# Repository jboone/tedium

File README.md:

# tedium

TDM telephony experimentation

## Dependencies

* `oss-cad-suite`: open-source digital design and verification tools, with [nightly binary builds](https://github.com/YosysHQ/oss-cad-suite-build).
* [`poetry`](https://python-poetry.org/): Python dependencies and packaging management tool.
* `g++-riscv64-linux-gnu`
* `rustup toolchain install stable -t riscv32i-unknown-none-elf`

## Installation

Clone this repository, and generally follow these steps:

```bash
$ cd tedium
# Grant access through `udev` to the FTDI JTAG interface on the Tedium board.
$ sudo ln -sf ./99-tedium.rules /etc/udev/rules.d/
$ sudo udevadm control --reload-rules && sudo udevadm trigger
#
$ pip3 install poetry --user
# Might need to log out and in to get ~/.local/bin in PATH.
# Or, `source ~/.profile`.
# Set up virtual environment, download and install dependencies
$ poetry install
# Enter poetry shell
$ poetry shell
# Include OSS CAD Suite tools in PATH
$ export PATH="/home/jboone/src/fpga/oss-cad-suite/bin:$PATH"
# Build and download FPGA bitstream
# LUNA_AVOID_BLOCKRAM required for reliable USB enumeration as of 2022/May/02.
$ LUNA_AVOID_BLOCKRAM=1 applets/tedium-fpga
# After the bitstream is generated, you can inspect the results in the `build` directory.
# Initialize the framer/LIU
$ cargo run --release --bin tedium-tool -- init
# Run the host-side audio and event engine
$ cargo run --release --bin tedium-tool -- monitor
```

NOTE: My Tedium .venv got weird when I had the "OSS CAD Suite" environment already enabled.
Poetry would download dependencies on `poetry install` or `poetry update`, but would then
delete them when running `poetry run` or `poetry shell`.

## Testing

Unit tests may be run like this:

```bash
$ python3 -m unittest tests.hdl.tx_usb_to_fifo
# Or the name of any other HDL test module you want to run/simulate.
```

## USB Debugging

```bash
$ sudo cat /sys/kernel/debug/usb/devices
$ sudo cat /sys/kernel/debug/dynamic_debug/control | grep "snd_usb_audio"
$ sudo echo 'file sound/usb/* +p' >/sys/kernel/debug/dynamic_debug/control
$ sudo sysctl -w kernel.printk=7 # debug-level messages
$ sudo sysctl kernel.printk
```

### Using Wireshark

```bash
$ sudo modprobe usbmon
$ sudo wireshark
# Capture stuff
```

Wireshark filters that might be of use:

```
# Find USB IN on endpoint 1, where the frame of completed inbound URBs is not the typical length.
# This helps find where the async audio input FIFO level is wrapping around.
usb.endpoint_address.number==1 && usb.endpoint_address.direction==IN && usb.urb_type=='C' && frame.len != 1728
# Set the time reference at an interesting record in Wireshark, disable view filtering, and work from there.
# Note that "marked" records appear regardless of whether they match the view filter, which is very handy.
# Now match on USB OUT records that have been submitted (pending transmission)
usb.endpoint_address.number==1 && usb.endpoint_address.direction==OUT && usb.urb_type=='S'
```

However, it seems like Wireshark isn't showing complete URB buffer contents?

## Trouble With Real-Time Kit

```bash
# Is there an `rtkit` user?
$ getent passwd rtkit
# Is there an `rtkit*` user?
$ ps ax | grep -i rtkit
# Check that RTKit is actually changing our process/thread priority:
$ journalctl -e -t rtkit-daemon
# `ulimit` values:
$ ulimit -a
```

## Use

See [the software README](tedium/README.md) for information on how to use `tedium-tool` to interact with the hardware over USB.

## License

This software and gateware in this project is licensed under the [BSD 3-Clause License](LICENSE-BSD-3-Clause).

The hardware is licensed under the [CERN Open Hardware Licence Version 2 - Permissive](LICENSE-CERN-OHL-P-v2).

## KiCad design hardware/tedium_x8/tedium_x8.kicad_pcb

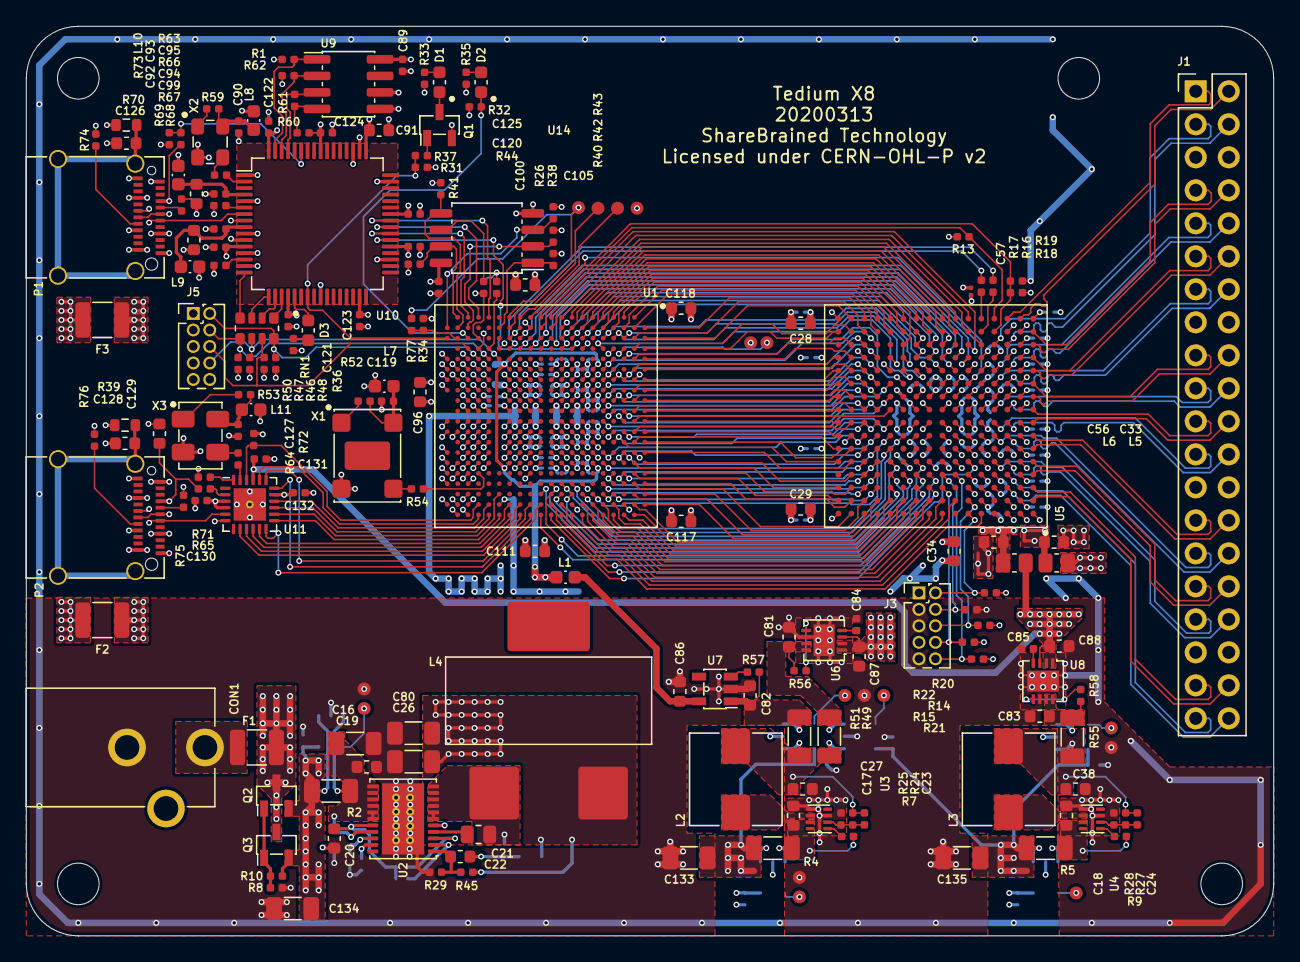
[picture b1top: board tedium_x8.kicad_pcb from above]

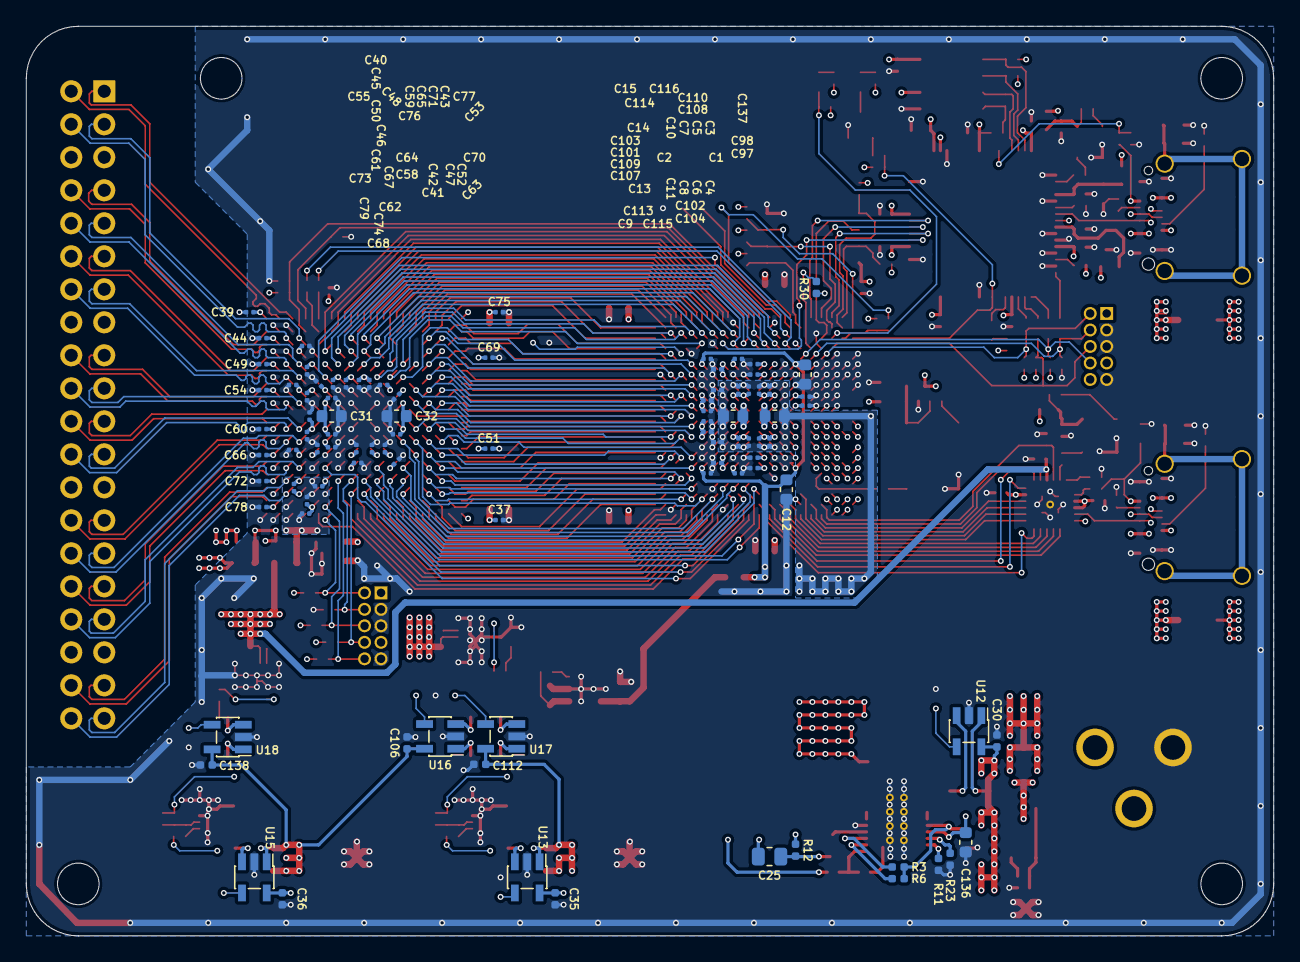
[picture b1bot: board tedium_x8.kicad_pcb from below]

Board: 4 copper layers, 96.0 x 70.0 mm, 283 parts (92 on the bottom side), 290 nets.

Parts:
C1, C2, C28, C29, C31, C32, C33, C34, C56, C91, C92, C93, C96, C105, C111, C117, C118: 10U; IPC_CAPC160X80X90L35N
C3, C4, C5, C6, C7, C8, C9, C10, C11, C13, C14, C15, C37, C39, C40, C41, C42, C43, C44, C45, C46, C47, C48, C49, C50, C51, C52, C53, C54, C55, C57, C58, C59, C60, C61, C62, C63, C64, C65, C66, C67, C68, C69, C70, C71, C72, C73, C74, C75, C76, C77, C78, C79, C97, C98, C101, C102, C103, C104, C107, C108, C109, C110, C113, C114, C115, C116: 100N; IPC_CAPC60X30X33L15N
C12, C20, C129, C137: 1U; IPC_CAPC160X80X90L35N
C16: 47U; IPC_CAPC320X160X180L55N
C17, C18, C19, C81, C82, C83, C86, C87, C88, C136: 4U7; IPC_CAPC160X80X90L35N
C21, C25: 100N; IPC_CAPC200X125X135L45N
C22: 1N2; IPC_CAPC160X80X90L35N
C23, C24: 120P; IPC_CAPC100X50X55L25N
C26, C80: 100U; IPC_CAPC320X160X180L55N
C27, C38: 22U; IPC_CAPC160X80X90L35N
C30, C35, C36, C89, C94, C95, C99, C100, C106, C112, C120, C121, C122, C123, C124, C125, C130, C131, C132, C138: 100N; IPC_CAPC100X50X55L25N
C84, C85: ?; IPC_CAPC100X50X55L25N
C90, C119, C127: 10N; IPC_CAPC100X50X55L25N
C126, C128: 100N; IPC_CAPC160X80X90L35N
C133, C134, C135: 22U; IPC_CAPC320X160X180L55N
CON1: BARREL_JACK; PJ-102AH
D1, D2, D3: LED; IPC_LEDC1608X90L40N
F1, F2, F3: Polyfuse_Small; IPC_FUSSC257X321X120L50N
H1, H2, H3, H4: MountingHole; MountingHole_3.2mm_M3
J1: Conn_02x20_Odd_Even; PinHeader_2x20_P2.54mm_Vertical
J3: DNP; PinHeader_2x05_P1.27mm_Vertical
J5: Conn_ARM_JTAG_SWD_10; PinHeader_2x05_P1.27mm_Vertical
L1, L7, L8, L9, L10, L11: L_Small; IPC_BEADC160X80X95L40N
L2, L3: 470N; WE-HCI_7050
L4: 1U; SER1590
L5, L6: L_Small; IPC_BEADC200X125X105L50N
P1, P2: USB_C; 12401610E4#2A
Q1: BC817; IPC_SOT23-3P95_237X112L50X42N
Q2, Q3: Q_PMOS_GSD; IPC_SOT23-3P95_237X112L50X42N
R1, R29, R31, R37, R41, R42, R43, R44, R52, R53, R59, R60, R62, R65, R69: 10K; IPC_RESC100X50X40L25N
R2: 0R01; IPC_RESC320X160X89L51N
R3, R6, R7, R9, R23, R25, R28, R56, R57, R58: 100K; IPC_RESC100X50X40L25N
R4, R5, R49, R51, R55: 0R1; IPC_RESC320X160X89L51N
R8, R10: 30K; IPC_RESC100X50X40L25N
R11: 68K1; IPC_RESC100X50X40L25N
R12: 432R; IPC_RESC100X50X40L25N
R13, R19, R30: 1K; IPC_RESC100X50X40L25N
R14, R15, R18, R20, R22: DNP; IPC_RESC100X50X40L25N
R16, R17, R54, R63, R64: 10R; IPC_RESC100X50X40L25N
R21, R32, R34, R38, R40, R46, R47, R48, R50, R68, R72: 4K7; IPC_RESC100X50X40L25N
R24: 536K; IPC_RESC100X50X40L25N
R26: 50R; IPC_RESC100X50X40L25N
R27: 280K; IPC_RESC100X50X40L25N
R33, R35, R36, R61, R67: 2K2; IPC_RESC100X50X40L25N
R39, R70: 330R; IPC_RESC160X80X55L25N
R45: 7K68; IPC_RESC100X50X40L25N
R66: 12K; IPC_RESC100X50X40L25N
R71: 8K06; IPC_RESC100X50X40L25N
R73, R74, R75, R76: 5K1; IPC_RESC100X50X40L25N
R77: 100R; IPC_RESC100X50X40L25N
RN1: 100R; IPC_RESCAXS8P80_320X160X60L30X45N
TP1: V1P1_I; TP_1MM
TP2: V3P8_I; TP_1MM
TP3: V2P3_I; TP_1MM
TP4: V3P3_I; TP_1MM
TP5: V2P5_I; TP_1MM
TP6: V1P8_I; TP_1MM
TP7, TP8, TP9, TP10: TestPoint; TP_1MM
TP11, TP12, TP13, TP14, TP15, TP16: GND; TP_1MM
U1: LFE5U-85F-8BG381; LATTICE_BGA_CABGA381
U2: TPS53318; IPC_SON23P50_600X500X150L50X27T547X324N
U3, U4: TPS62823; IPC_SON8P50_200X150X100L35X25N
U5: XRT86VX38; IPC_BGA256CP100_16X16_1700X1700X178B55N
U6: ADM7171ACPZ-3.3-R7; IPC_SON9P50_300X300X80L40X25T244X160N
U7: ADP150AUJZ-2.5-R7; IPC_SOT23-5P95_280X100L45X40N
U8: ADM7171ACPZ-1.8-R7; IPC_SON9P50_300X300X80L40X25T244X160N
U9: 93LC46C; IPC_SOIC8P127_490X600X175L83X41N
U10: FT2232H; IPC_QFP64P50_1200X1200X160L60X22N
U11: USB3317C-CP; IPC_QFN25P50_400X400X100L40X24T250N
U12, U17: INA180B3; TI_DBV_SOT-23-5
U13, U15, U16, U18: INA180B2; TI_DBV_SOT-23-5
U14: QSPI8; IPC_SOIC8P127_528X790X216L65X41N
X1: 16M384; ASVMB
X2: 12M; IPC_OSCCC320X250X120L75X100N
X3: 26M; IPC_OSCSC4P254_500X320X140L100X120N

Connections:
+5V: C30.1, C35.1, C36.1, C106.1, C112.1, C133.1, C134.1, C135.1, C138.1, Q2.2, Q3.2, R2.2, R4.2, R5.2, R10.2, U12.1, U12.5, U13.1, U13.5, U15.1, U15.5, U16.5, U17.5, U18.5
/fpga_bank/8KEXTOSC: U1.M1, U5.L6
/fpga_bank/A0: U1.E9, U5.L13
/fpga_bank/A1: U1.C9, U5.L14
/fpga_bank/A2: U1.B9, U5.K15
/fpga_bank/A3: U1.C5, U5.L11
/fpga_bank/A4: U1.D9, U5.K13
/fpga_bank/A5: U1.A9, U5.K16
/fpga_bank/A6: U1.E10, U5.K14
/fpga_bank/A7: U1.B10, U5.J15
/fpga_bank/A8: U1.C10, U5.J14
/fpga_bank/A9: U1.C11, U5.J13
/fpga_bank/A10: U1.D13, U5.H14
/fpga_bank/A11: U1.A11, U5.H16
/fpga_bank/A12: U1.A12, U5.G16
/fpga_bank/A13: U1.B13, U5.F16
/fpga_bank/A14: U1.H17, U5.G11
/fpga_bank/ACK0#: U1.A5, U5.N15
/fpga_bank/ACK1#: U1.A6, U5.M15
/fpga_bank/ALE: U1.A10, U5.J16
/fpga_bank/CLKREF: R54.2, U1.U16
/fpga_bank/CS#: U1.C14, U5.F14
/fpga_bank/D0: U1.E8, U5.M14
/fpga_bank/D1: U1.D10, U5.L12
/fpga_bank/D2: U1.E11, U5.K12
/fpga_bank/D3: U1.B11, U5.J12
/fpga_bank/D4: U1.C12, U5.H13
/fpga_bank/D5: U1.E14, U5.G14
/fpga_bank/D6: U1.F18, U5.G12
/fpga_bank/D7: U1.C15, U5.G13
/fpga_bank/E1OSCCLK: R16.1, U1.P4
/fpga_bank/FPGA_C4: TP10.1, U1.C4
/fpga_bank/FPGA_N1: TP7.1, U1.N1
/fpga_bank/FPGA_P2: TP9.1, U1.P2
/fpga_bank/FRM_RESET#: R18.1, R19.2, U1.L1, U5.R4
/fpga_bank/FT_SCLK: U1.H4, U10.38
/fpga_bank/INT#: U1.B12, U5.H15
/fpga_bank/MCLKIN: U1.K20, U5.E6
/fpga_bank/PCLK: U1.A7, U5.M16
/fpga_bank/PROGRAMN: R77.1, TP8.1, U1.P1
/fpga_bank/PTYPE0: U1.D7, U5.M13
/fpga_bank/PTYPE2: U1.D12, U5.H12
/fpga_bank/RD#: U1.B8, U5.L15
/fpga_bank/RDY#: U1.A8, U5.L16
/fpga_bank/REQ0#: U1.B6, U5.N16
/fpga_bank/REQ1#: U1.A4, U5.R16
/fpga_bank/RXCASYNC0: U1.F20, U5.A9
/fpga_bank/RXCASYNC1: U1.K17, U5.D11
/fpga_bank/RXCASYNC2: U1.E17, U5.D13
/fpga_bank/RXCASYNC3: U1.C16, U5.E13
/fpga_bank/RXCASYNC4: U1.B3, U5.R14
/fpga_bank/RXCASYNC5: U1.C2, U5.R12
/fpga_bank/RXCASYNC6: U1.J3, U5.N9
/fpga_bank/RXCASYNC7: U1.F3, U5.M8
/fpga_bank/RXCRCSYNC0: U1.G20, U5.A8
/fpga_bank/RXCRCSYNC1: U1.L20, U5.C10
/fpga_bank/RXCRCSYNC2: U1.E18, U5.C14
/fpga_bank/RXCRCSYNC3: U1.J17, U5.E12
/fpga_bank/RXCRCSYNC4: U1.B4, U5.R15
/fpga_bank/RXCRCSYNC5: U1.B2, U5.R13
/fpga_bank/RXCRCSYNC6: U1.F2, U5.R9
/fpga_bank/RXCRCSYNC7: U1.M4, U5.N7
/fpga_bank/RXSCLK0: U1.E19, U5.B10
/fpga_bank/RXSCLK1: U1.J18, U5.D12
/fpga_bank/RXSCLK2: U1.B17, U5.A15
/fpga_bank/RXSCLK3: U1.G18, U5.F12
/fpga_bank/RXSCLK4: U1.A3, U5.T15
/fpga_bank/RXSCLK5: U1.D1, U5.T11
/fpga_bank/RXSCLK6: U1.J4, U5.P9
/fpga_bank/RXSCLK7: U1.K3, U5.M7
/fpga_bank/RXSER0: U1.H20, U5.B7
/fpga_bank/RXSER1: U1.D19, U5.B11
/fpga_bank/RXSER2: U1.A18, U5.B14
/fpga_bank/RXSER3: U1.B16, U5.B16
/fpga_bank/RXSER4: U1.B5, U5.P15
/fpga_bank/RXSER5: U1.E2, U5.P11
/fpga_bank/RXSER6: U1.E1, U5.T10
/fpga_bank/RXSER7: U1.L4, U5.P8
/fpga_bank/RXSERCLK0: U1.G19, U5.B8
/fpga_bank/RXSERCLK1: U1.E20, U5.A10
/fpga_bank/RXSERCLK2: U1.D18, U5.C13
/fpga_bank/RXSERCLK3: U1.A15, U5.D15
/fpga_bank/RXSERCLK4: U1.E7, U5.P14
/fpga_bank/RXSERCLK5: U1.C1, U5.T12
/fpga_bank/RXSERCLK6: U1.C3, U5.M10
/fpga_bank/RXSERCLK7: U1.J1, U5.R6
/fpga_bank/RXSYNC0: U1.F19, U5.B9
/fpga_bank/RXSYNC1: U1.D20, U5.A11
/fpga_bank/RXSYNC2: U1.B19, U5.A13
/fpga_bank/RXSYNC3: U1.B15, U5.C16
/fpga_bank/RXSYNC4: U1.C7, U5.N13
/fpga_bank/RXSYNC5: U1.E3, U5.N11
/fpga_bank/RXSYNC6: U1.F1, U5.T9
/fpga_bank/RXSYNC7: U1.H2, U5.R7
/fpga_bank/RXTSEL: U1.J19, U5.A5
/fpga_bank/T1OSCCLK: R17.1, U1.P3
/fpga_bank/TXMSYNC0: U1.J20, U5.D9
/fpga_bank/TXMSYNC1: U1.C20, U5.A12
/fpga_bank/TXMSYNC2: U1.A16, U5.C15
/fpga_bank/TXMSYNC3: U1.C17, U5.E14
/fpga_bank/TXMSYNC4: U1.E6, U5.P13
/fpga_bank/TXMSYNC5: U1.D2, U5.R11
/fpga_bank/TXMSYNC6: U1.G2, U5.R8
/fpga_bank/TXMSYNC7: U1.N4, U5.N6
/fpga_bank/TXON: R13.2, U1.L2, U5.T4
/fpga_bank/TXSER0: U1.L18, U5.E10
/fpga_bank/TXSER1: U1.H18, U5.C12
/fpga_bank/TXSER2: U1.D16, U5.D14
/fpga_bank/TXSER3: U1.A13, U5.F15
/fpga_bank/TXSER4: U1.D3, U5.N12
/fpga_bank/TXSER5: U1.H3, U5.P10
/fpga_bank/TXSER6: U1.G1, U5.T8
/fpga_bank/TXSER7: U1.K1, U5.P5
/fpga_bank/TXSERCLK0: U1.K18, U5.D10
/fpga_bank/TXSERCLK1: U1.A19, U5.B13
/fpga_bank/TXSERCLK2: U1.A17, U5.B15
/fpga_bank/TXSERCLK3: U1.C13, U5.E16
/fpga_bank/TXSERCLK4: U1.A2, U5.T14
/fpga_bank/TXSERCLK5: U1.G3, U5.N10
/fpga_bank/TXSERCLK6: U1.H1, U5.T7
/fpga_bank/TXSERCLK7: U1.N3, U5.P6
/fpga_bank/TXSYNC0: U1.K19, U5.C9
/fpga_bank/TXSYNC1: U1.B20, U5.B12
/fpga_bank/TXSYNC2: U1.B18, U5.A14
/fpga_bank/TXSYNC3: U1.A14, U5.E15
/fpga_bank/TXSYNC4: U1.B1, U5.T13
/fpga_bank/TXSYNC5: U1.E4, U5.M11
/fpga_bank/TXSYNC6: U1.L3, U5.N8
/fpga_bank/TXSYNC7: U1.K2, U5.T6
/fpga_bank/ULPI_CLKOUT: U1.L19, U11.12
/fpga_bank/ULPI_DATA0: U1.T19, U11.16
/fpga_bank/ULPI_DATA1: U1.T20, U11.15
/fpga_bank/ULPI_DATA2: U1.R18, U11.14
/fpga_bank/ULPI_DATA3: U1.R20, U11.13
/fpga_bank/ULPI_DATA4: U1.P19, U11.11
/fpga_bank/ULPI_DATA5: U1.P20, U11.10
/fpga_bank/ULPI_DATA6: U1.N19, U11.9
/fpga_bank/ULPI_DATA7: U1.N20, U11.8
/fpga_bank/ULPI_DIR: U1.M19, U11.19
/fpga_bank/ULPI_DM: P2.A7, P2.B7, U11.5
/fpga_bank/ULPI_DP: P2.A6, P2.B6, U11.6
/fpga_bank/ULPI_NXT: U1.M20, U11.18
/fpga_bank/ULPI_REFCLK: R64.2, U11.23
/fpga_bank/ULPI_RESETB: R72.1, U1.U19, U11.22
/fpga_bank/ULPI_SHIELD: C128.2, P2.SH, R39.1
/fpga_bank/ULPI_STP: U1.U20, U11.20
/fpga_bank/VBUS_ULPI: C129.2, F2.2, P2.A4, P2.A9, P2.B4, P2.B9, R65.2
/fpga_bank/WR#: U1.E15, U5.F13
/fpga_cfg/ADBUS0: RN1.8, U10.16
/fpga_cfg/ADBUS1: RN1.7, U10.17
/fpga_cfg/ADBUS2: RN1.6, U10.18
/fpga_cfg/ADBUS3: RN1.5, U10.19
/fpga_cfg/CFG1: R38.2, U1.T4
/fpga_cfg/CSSPIN: R40.2, U1.R2, U14.1
/fpga_cfg/DONE: R31.2, R37.2, U1.Y3, U10.23
/fpga_cfg/FT_CS: U1.T1, U10.41
/fpga_cfg/FT_DM: P1.A7, P1.B7, U10.7
/fpga_cfg/FT_DP: P1.A6, P1.B6, U10.8
/fpga_cfg/FT_EECLK: R62.2, U9.2, U10.62
/fpga_cfg/FT_EECS: R1.2, U9.1, U10.63
/fpga_cfg/FT_EEDATA: R61.1, U9.3, U10.61
/fpga_cfg/FT_MISO: U1.U1, U10.40
/fpga_cfg/FT_MOSI: U1.V1, U10.39
/fpga_cfg/FT_OSCI: R63.2, U10.2
/fpga_cfg/FT_PWRSAV#: R68.2, R69.1, U10.59
/fpga_cfg/FT_RESET#: R67.2, U10.14
/fpga_cfg/FT_SHIELD: C126.2, P1.SH, R70.1
/fpga_cfg/FT_V1P8_LDO: C91.1, C99.2, C120.2, C122.2, U10.12, U10.37, U10.49, U10.64
/fpga_cfg/INITN: D2.C, R32.2, U1.V3
/fpga_cfg/IO2: R43.2, U1.Y2, U14.3
/fpga_cfg/IO3: R44.2, U1.W1, U14.7
/fpga_cfg/JTAG_ACT: D3.C, U10.21
/fpga_cfg/MCLK: R26.2, U14.6
/fpga_cfg/MISO: R42.2, U1.V2, U14.2
/fpga_cfg/MOSI: R41.2, U1.W2, U14.5
/fpga_cfg/TCK: J5.4, R50.1, RN1.1, U1.T5
/fpga_cfg/TDI: J5.8, R47.2, RN1.2, U1.R5
/fpga_cfg/TDO: J5.6, R46.2, RN1.3, U1.V4
/fpga_cfg/TMS: J5.2, R48.2, RN1.4, U1.U5
/fpga_cfg/VBUS_FT: F3.2, P1.A4, P1.A9, P1.B4, P1.B9, R68.1
/framer/RRING0: J1.37, U5.C1
/framer/RRING1: J1.31, U5.E1
/framer/RRING2: J1.27, U5.G1
/framer/RRING3: J1.21, U5.J1
/framer/RRING4: J1.17, U5.L1
/framer/RRING5: J1.11, U5.N1
/framer/RRING6: J1.7, U5.R1
/framer/RRING7: J1.1, U5.T3
/framer/RTIP0: J1.38, U5.B1
/framer/RTIP1: J1.32, U5.D1
/framer/RTIP2: J1.28, U5.F1
/framer/RTIP3: J1.22, U5.H1
/framer/RTIP4: J1.18, U5.K1
/framer/RTIP5: J1.12, U5.M1
/framer/RTIP6: J1.8, U5.P1
/framer/RTIP7: J1.2, U5.T2
/framer/TCK: J3.4, R22.2, U5.D8
/framer/TDI: J3.8, R15.1, U5.C8
/framer/TDO: J3.6, R14.1, U5.B6
/framer/TMS: J3.2, R20.1, U5.A6
/framer/TRING0: J1.39, U5.D3
/framer/TRING1: J1.33, U5.E4
/framer/TRING2: J1.29, U5.G4
/framer/TRING3: J1.23, U5.H4
/framer/TRING4: J1.19, U5.J4
/framer/TRING5: J1.13, U5.L4
/framer/TRING6: J1.9, U5.M4
/framer/TRING7: J1.3, U5.P4
/framer/TRST: J3.10, R21.1, U5.D7
/framer/TTIP0: J1.40, U5.C3
/framer/TTIP1: J1.34, U5.E3
/framer/TTIP2: J1.30, U5.G3
/framer/TTIP3: J1.24, U5.H3
/framer/TTIP4: J1.20, U5.J3
/framer/TTIP5: J1.14, U5.L3
/framer/TTIP6: J1.10, U5.M3
/framer/TTIP7: J1.4, U5.P3
/power/FPGA_V1P1: C1.1, C2.1, C3.1, C4.1, C5.1, C6.1, C7.1, C8.1, C10.1, C11.1, C13.1, C14.1, C25.2, C26.1, C80.1, L4.2, R45.1, U1.H8, U1.H9, U1.H10, U1.H11, U1.H12, U1.H13, U1.J8, U1.J13, U1.K8, U1.K13, U1.L8, U1.L13, U1.M8, U1.M13, U1.N8, U1.N9, U1.N10, U1.N11, U1.N12, U1.N13
/power/FPGA_V2P5: C86.1, L1.1, U7.5
/power/FRAMER_V1P8: C31.1, C32.1, C42.1, C43.1, C47.1, C48.1, C52.1, C53.1, C58.1, C59.1, C64.1, C65.1, C70.1, C71.1, C76.1, C77.1, C88.1, C131.2, L6.1, U5.F8, U5.F9, U5.F10, U5.G6, U5.H6, U5.H11, U5.J6, U5.J11, U5.K6, U5.K11, U5.L7, U5.L8, U5.L9, U5.L10, U8.1, U8.2, U8.3, U11.21
/power/FRAMER_V3P3: C28.1, C29.1, C34.1, C37.1, C40.1, C41.1, C45.1, C46.1, C50.1, C51.1, C55.1, C57.1, C61.1, C63.1, C67.1, C69.1, C73.1, C75.1, C79.1, C87.1, C89.1, C96.1, C97.1, C98.1, C100.1, C101.1, C102.1, C103.1, C104.1, C105.1, C107.1, C108.1, C109.1, C110.1, C111.1, C113.1, C114.1, C115.1, C116.1, C117.1, C118.1, C121.2, C123.2, C124.2, C125.2, C130.2, C132.2, J3.1, J5.1, L5.1, L7.1, L8.1, L9.1, L10.1, L11.1, R1.1, R14.2, R15.2, R18.2, R20.2, R21.2, R30.1, R31.1, R32.1, R33.1, R34.1, R35.1, R36.2, R38.1, R40.1, R41.1, R42.1, R43.1, R44.1, R46.1, R47.1, R48.1, R60.1, R62.1, R67.1, U1.F9, U1.F10, U1.F11, U1.F12, U1.H6, U1.H7, U1.H14, U1.H15, U1.J6, U1.J15, U1.L6, U1.L7, U1.L14, U1.L15, U1.M6, U1.M15, U1.P9, U1.P10, U5.A16, U5.D4, U5.E8, U5.E11, U5.F4, U5.F5, U5.G15, U5.H5, U5.K4, U5.K5, U5.M5, U5.M6, U5.M9, U5.N4, U5.N14, U5.T16, U6.1, U6.2, U6.3, U9.6, U9.8, U10.20, U10.31, U10.42, U10.50, U10.56, U11.3, U11.4, U11.17, U14.8
/power/V1P8_FRM_PLL: C56.1, C62.1, C68.1, C74.1, L6.2, U5.A3, U5.A4, U5.B3, U5.C5, U5.C6, U5.D5
/power/V3P3_FRM_RX: C33.1, C39.1, C44.1, C49.1, C54.1, C60.1, C66.1, C72.1, C78.1, L5.2, U5.B2, U5.D2, U5.F2, U5.H2, U5.K2, U5.M2, U5.P2, U5.T1
/power/VCCAUX: C9.1, C12.1, C15.1, C137.1, L1.2, U1.F6, U1.F15, U1.P6, U1.P15
/regulator/V1P1_EN: R6.1, U2.2
/regulator/V1P1_LL: C21.2, L4.1, R12.1, U2.6, U2.7, U2.8, U2.9, U2.10, U2.11
/regulator/V1P1_MODE: R23.1, U2.20
/regulator/V1P1_PGOOD: R3.1, U2.3
/regulator/V1P1_SW_IN: C16.2, C19.2, C136.2, R2.1, U2.12, U2.13, U2.14, U2.15, U2.16, U2.17, U2.19, U12.3
/regulator/V1P1_TRIP: R11.1, U2.21
/regulator/V1P1_VBST: C21.1, U2.4
/regulator/V1P1_VFB: C22.1, R29.2, R45.2, U2.1
/regulator/V1P1_VREG: C20.2, R3.2, R6.2, U2.18
/regulator/V1P8_LDO_IN: C83.1, R55.1, R58.1, U8.7, U8.8, U18.3
/regulator/V2P3_SW: L3.1, U4.6
/regulator/V2P3_SW_IN: C18.1, R5.1, R9.2, U4.7, U15.3
/regulator/V2P3_SW_OUT: C24.1, C38.1, L3.2, R27.2, R55.2, U18.1
/regulator/V2P5_LDO_IN: C82.2, R51.1, R57.2, U7.1, U17.3
/regulator/V3P3_LDO_IN: C81.2, R49.1, R56.1, U6.7, U6.8, U16.3
/regulator/V3P8_SW: L2.1, U3.6
/regulator/V3P8_SW_IN: C17.2, R4.1, R7.2, U3.7, U13.3
/regulator/V3P8_SW_OUT: C23.1, C27.1, L2.2, R24.2, R49.2, R51.2, U16.1, U17.1
/regulator/VRAW: CON1.1, F1.2
/regulator/VRAW_FUSED: F1.1, F2.1, F3.1, Q2.3, Q3.3
GND: C1.2, C2.2, C3.2, C4.2, C5.2, C6.2, C7.2, C8.2, C9.2, C10.2, C11.2, C12.2, C13.2, C14.2, C15.2, C16.1, C17.1, C18.2, C19.1, C20.1, C26.2, C27.2, C28.2, C29.2, C30.2, C31.2, C32.2, C33.2, C34.2, C35.2, C36.2, C37.2, C38.2, C39.2, C40.2, C41.2, C42.2, C43.2, C44.2, C45.2, C46.2, C47.2, C48.2, C49.2, C50.2, C51.2, C52.2, C53.2, C54.2, C55.2, C56.2, C57.2, C58.2, C59.2, C60.2, C61.2, C62.2, C63.2, C64.2, C65.2, C66.2, C67.2, C68.2, C69.2, C70.2, C71.2, C72.2, C73.2, C74.2, C75.2, C76.2, C77.2, C78.2, C79.2, C80.2, C81.1, C82.1, C83.2, C84.2, C85.2, C86.2, C87.2, C88.2, C89.2, C90.1, C91.2, C92.2, C93.2, C94.1, C95.1, C96.2, C97.2, C98.2, C99.1, C100.2, C101.2, C102.2, C103.2, C104.2, C105.2, C106.2, C107.2, C108.2, C109.2, C110.2, C111.2, C112.2, C113.2, C114.2, C115.2, C116.2, C117.2, C118.2, C119.1, C120.1, C121.1, C122.1, C123.1, C124.1, C125.1, C126.1, C127.1, C128.1, C129.1, C130.1, C131.1, C132.1, C133.2, C134.2, C135.2, C136.1, C137.2, C138.2, CON1.2, J1.5, J1.6, J1.15, J1.16, J1.25, J1.26, J1.35, J1.36, J3.3, J3.5, J3.9, J5.3, J5.5, J5.9, P1.A1, P1.A12, P1.B1, P1.B12, P2.A1, P2.A12, P2.B1, P2.B12, Q1.2, R8.1, R11.2, R13.1, R19.1, R22.1, R23.2, R25.1, R28.1, R29.1, R39.2, R50.2, R66.1, R69.2, R70.2, R71.1, R72.2, R73.2, R74.2, R75.2, R76.2, TP11.1, TP12.1, TP13.1, TP14.1, TP15.1, TP16.1, U1.B7, U1.B14, U1.C19, U1.D4, U1.F7, U1.F8, U1.F13, U1.F14, U1.G4, U1.G6, U1.G7, U1.G8, U1.G9, U1.G10, U1.G11, U1.G12, U1.G13, U1.G14, U1.G15, U1.G17, U1.H19, U1.J2, U1.J7, U1.J9, U1.J10, U1.J11, U1.J12, U1.J14, U1.K6, U1.K7, U1.K9, U1.K10, U1.K11, U1.K12, U1.K14, U1.K15, U1.L9, U1.L10, U1.L11, U1.L12, U1.M2, U1.M7, U1.M9, U1.M10, U1.M11, U1.M12, U1.M14, U1.M16, U1.N6, U1.N7, U1.N14, U1.N15, U1.P7, U1.P8, U1.P11, U1.P12, U1.P13, U1.P14, U1.R4, U1.R19, U1.T6, U1.T7, U1.T8, U1.T9, U1.T10, U1.T11, U1.T12, U1.T13, U1.T14, U1.T15, U1.U4, U1.U6, U1.U7, U1.U8, U1.U9, U1.U10, U1.U11, U1.U12, U1.U13, U1.U14, U1.U15, U1.V5, U1.V6, U1.V7, U1.V8, U1.V9, U1.V10, U1.V11, U1.V12, U1.V13, U1.V14, U1.V15, U1.V16, U1.V17, U1.V18, U1.V19, U1.V20, U1.W6, U1.W7, U1.W12, U1.W15, U1.W16, U1.W19, U1.W20, U1.Y5, U1.Y6, U1.Y7, U1.Y8, U1.Y11, U1.Y12, U1.Y14, U1.Y15, U1.Y16, U1.Y17, U1.Y19, U2.5, U2.23, U3.3, U3.5, U4.3, U4.5, U5.A1, U5.A2, U5.B5, U5.C2, U5.C4, U5.D6, U5.E2, U5.E5, U5.E7, U5.E9, U5.F3, U5.F6, U5.F7, U5.G2, U5.G5, U5.G7, U5.G8, U5.G9, U5.G10, U5.H7, U5.H8, U5.H9, U5.H10, U5.J2, U5.J5, U5.J7, U5.J8, U5.J9, U5.J10, U5.K3, U5.K7, U5.K8, U5.K9, U5.K10, U5.L2, U5.L5, U5.M12, U5.N2, U5.N3, U5.N5, U5.R2, U5.R3, U6.6, U6.9, U7.2, U8.6, U8.9, U9.5, U10.1, U10.5, U10.10, U10.11, U10.13, U10.15, U10.25, U10.35, U10.47, U10.51, U11.25, U12.2, U13.2, U14.4, U15.2, U16.2, U17.2, U18.2, X1.2, X2.2, X3.2
unnamed: C22.2, C25.1, R12.2
unnamed: C23.2, R24.1, R25.2, U3.2
unnamed: C24.2, R27.1, R28.2, U4.2
unnamed: C84.1, U6.4
unnamed: C85.1, U8.4
unnamed: C90.2, L8.2, R59.2, X2.4
unnamed: C92.1, C94.2, L9.2, U10.9
unnamed: C93.1, C95.2, L10.2, U10.4
unnamed: C119.2, L7.2, R52.2, X1.4
unnamed: C127.2, L11.2, R53.2, X3.4
unnamed: D1.A, R33.2
unnamed: D1.C, Q1.3
unnamed: D2.A, R35.2
unnamed: D3.A, R36.1
unnamed: P1.A5, R73.1
unnamed: P1.B5, R74.1
unnamed: P2.A5, R75.1
unnamed: P2.B5, R76.1
unnamed: Q1.1, R37.1
unnamed: Q2.1, Q3.1, R8.2, R10.1
unnamed: R7.1, U3.1
unnamed: R9.1, U4.1
unnamed: R16.2, U5.R5
unnamed: R17.2, U5.T5
unnamed: R26.1, R30.2, U1.U3
unnamed: R34.2, R77.2, U1.W3
unnamed: R52.1, X1.1
unnamed: R53.1, X3.1
unnamed: R54.1, X1.3
unnamed: R56.2, U6.5
unnamed: R57.1, U7.3
unnamed: R58.2, U8.5
unnamed: R59.1, X2.1
unnamed: R60.2, R61.2, U9.4
unnamed: R63.1, X2.3
unnamed: R64.1, X3.3
unnamed: R65.1, U11.2
unnamed: R66.2, U10.6
unnamed: R71.2, U11.24
unnamed: TP1.1, U12.4
unnamed: TP2.1, U13.4
unnamed: TP3.1, U15.4
unnamed: TP4.1, U16.4
unnamed: TP5.1, U17.4
unnamed: TP6.1, U18.4

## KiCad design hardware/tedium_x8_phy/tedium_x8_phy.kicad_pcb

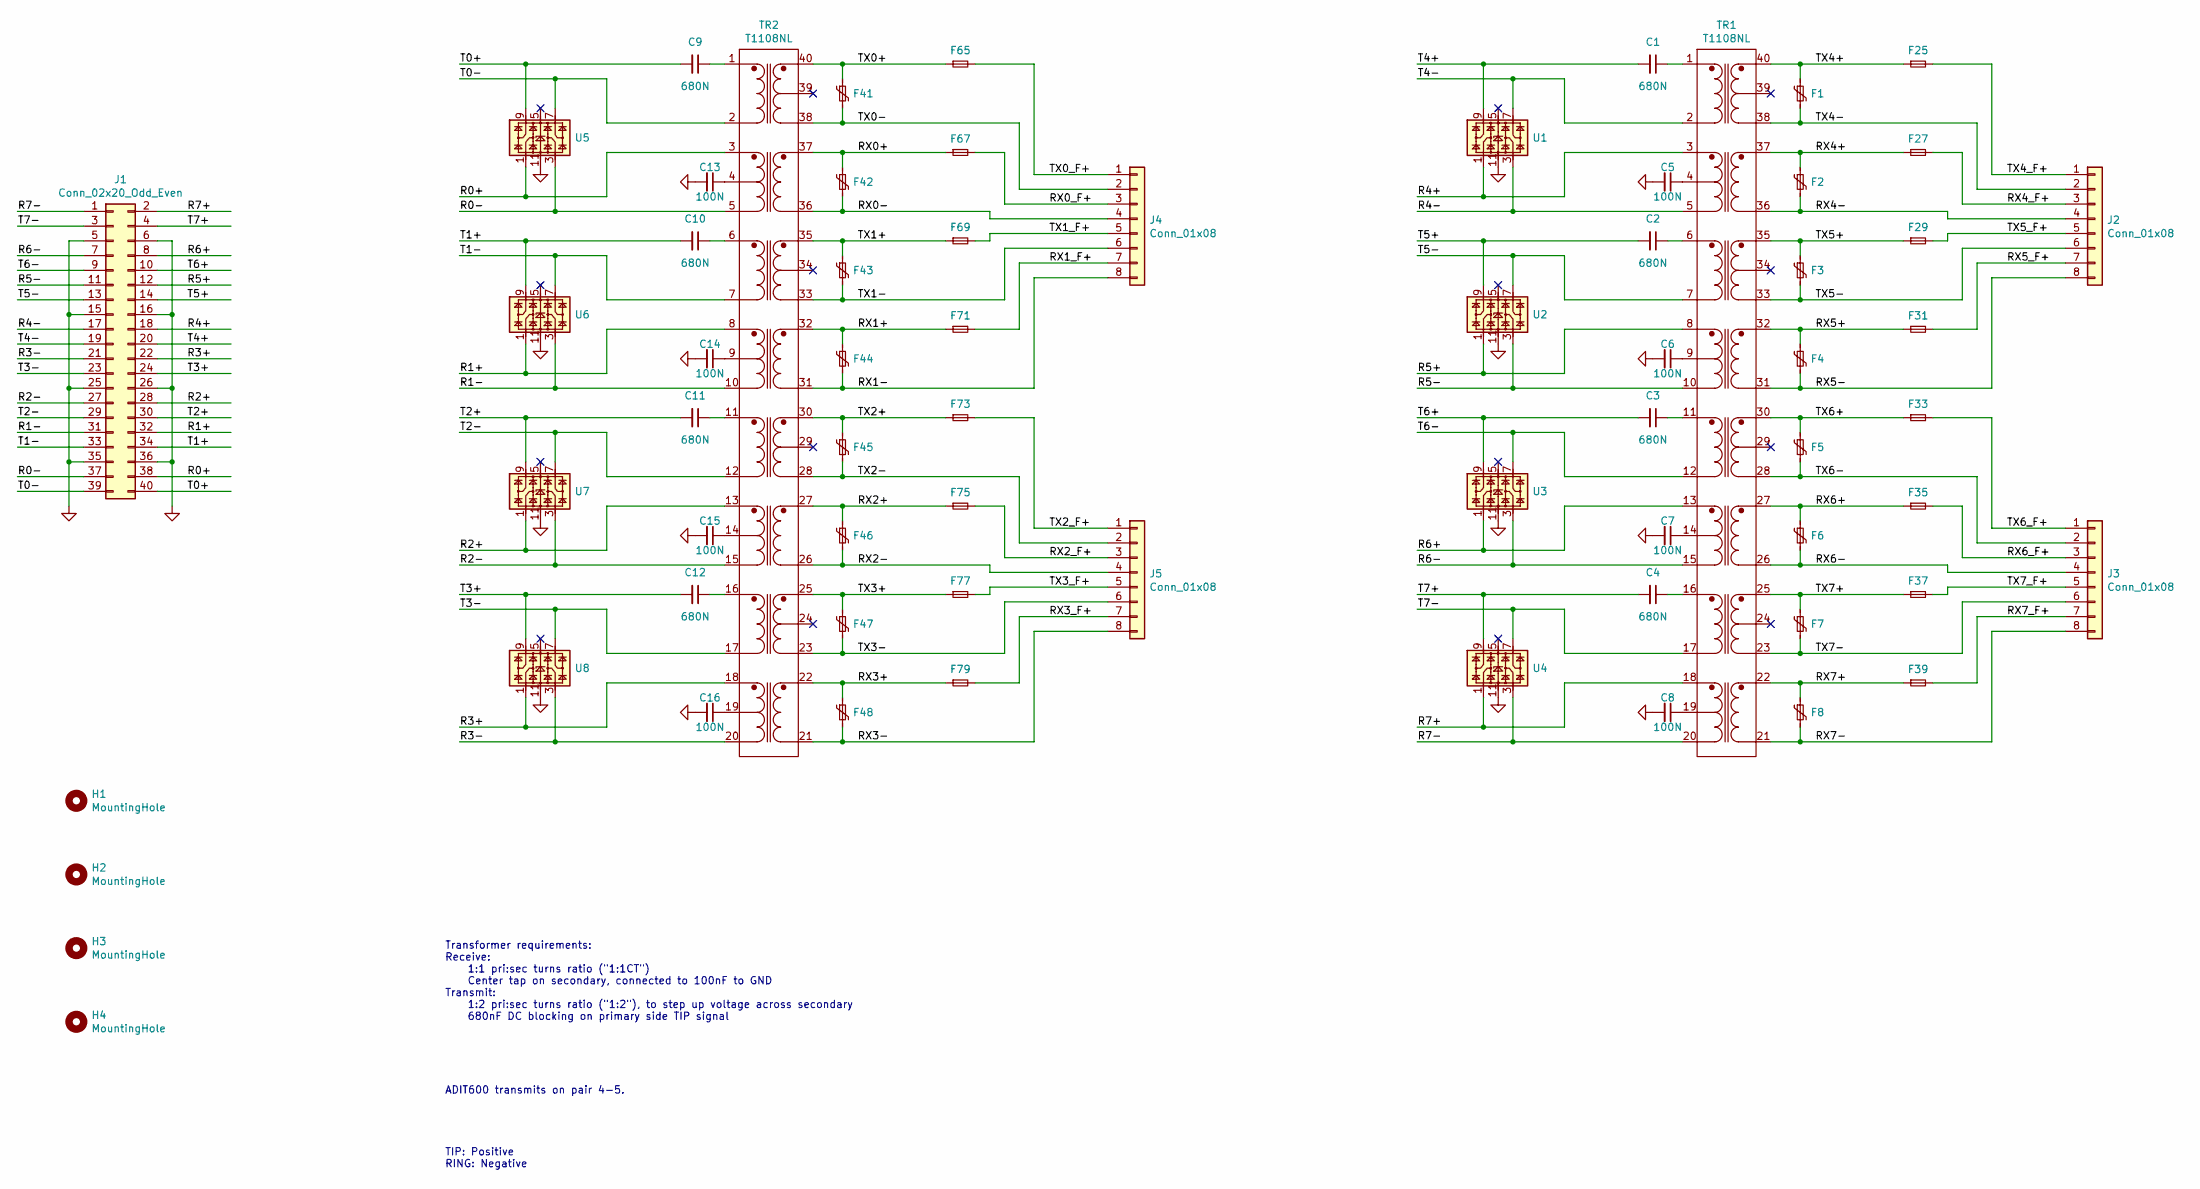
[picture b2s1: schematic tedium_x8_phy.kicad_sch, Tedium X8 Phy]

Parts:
C1, C2, C3, C4, C9, C10, C11, C12: 680N; IPC_CAPC200X125X135L45N; Part GCM21BR71E684KA55L
C5, C6, C7, C8, C13, C14, C15, C16: 100N; IPC_CAPC160X80X90L35N; Part GRM188R71C104KA01D
F1, F2, F3, F4, F5, F6, F7, F8, F41, F42, F43, F44, F45, F46, F47, F48: Polyfuse_Small; DO-214AA; Part ‎P0080SCMCLRP‎
F25, F27, F29, F31, F33, F35, F37, F39, F65, F67, F69, F71, F73, F75, F77, F79: Fuse_Small; 461; Part 04611.25ER
H1, H2, H3, H4: MountingHole; MountingHole_3.2mm_M3
J1: Conn_02x20_Odd_Even; PinHeader_2x20_P2.54mm_Vertical
J2, J3, J4, J5: Conn_01x08; SS-51000-003; Part SS-51000-003
TR1, TR2: T1108NL; TOU; Part T1108NL
U1, U2, U3, U4, U5, U6, U7, U8: RClamp3304NA; IPC_SON11P50_260X260X65L35X25T215X126N; Part RClamp3304NA

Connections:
/R0+: J1.38, TR2.3, U5.1
/R0-: J1.37, TR2.5, U5.3
/R1+: J1.32, TR2.8, U6.1
/R1-: J1.31, TR2.10, U6.3
/R2+: J1.28, TR2.13, U7.1
/R2-: J1.27, TR2.15, U7.3
/R3+: J1.22, TR2.18, U8.1
/R3-: J1.21, TR2.20, U8.3
/R4+: J1.18, TR1.3, U1.1
/R4-: J1.17, TR1.5, U1.3
/R5+: J1.12, TR1.8, U2.1
/R5-: J1.11, TR1.10, U2.3
/R6+: J1.8, TR1.13, U3.1
/R6-: J1.7, TR1.15, U3.3
/R7+: J1.2, TR1.18, U4.1
/R7-: J1.1, TR1.20, U4.3
/RX0+: F42.1, F67.1, TR2.37
/RX0-: F42.2, J4.4, TR2.36
/RX0_F+: F67.2, J4.3
/RX1+: F44.1, F71.1, TR2.32
/RX1-: F44.2, J4.8, TR2.31
/RX1_F+: F71.2, J4.7
/RX2+: F46.1, F75.1, TR2.27
/RX2-: F46.2, J5.4, TR2.26
/RX2_F+: F75.2, J5.3
/RX3+: F48.1, F79.1, TR2.22
/RX3-: F48.2, J5.8, TR2.21
/RX3_F+: F79.2, J5.7
/RX4+: F2.1, F27.1, TR1.37
/RX4-: F2.2, J2.4, TR1.36
/RX4_F+: F27.2, J2.3
/RX5+: F4.1, F31.1, TR1.32
/RX5-: F4.2, J2.8, TR1.31
/RX5_F+: F31.2, J2.7
/RX6+: F6.1, F35.1, TR1.27
/RX6-: F6.2, J3.4, TR1.26
/RX6_F+: F35.2, J3.3
/RX7+: F8.1, F39.1, TR1.22
/RX7-: F8.2, J3.8, TR1.21
/RX7_F+: F39.2, J3.7
/T0+: C9.2, J1.40, U5.9
/T0-: J1.39, TR2.2, U5.7
/T1+: C10.2, J1.34, U6.9
/T1-: J1.33, TR2.7, U6.7
/T2+: C11.2, J1.30, U7.9
/T2-: J1.29, TR2.12, U7.7
/T3+: C12.2, J1.24, U8.9
/T3-: J1.23, TR2.17, U8.7
/T4+: C1.2, J1.20, U1.9
/T4-: J1.19, TR1.2, U1.7
/T5+: C2.2, J1.14, U2.9
/T5-: J1.13, TR1.7, U2.7
/T6+: C3.2, J1.10, U3.9
/T6-: J1.9, TR1.12, U3.7
/T7+: C4.2, J1.4, U4.9
/T7-: J1.3, TR1.17, U4.7
/TX0+: F41.1, F65.1, TR2.40
/TX0-: F41.2, J4.2, TR2.38
/TX0_F+: F65.2, J4.1
/TX1+: F43.1, F69.1, TR2.35
/TX1-: F43.2, J4.6, TR2.33
/TX1_F+: F69.2, J4.5
/TX2+: F45.1, F73.1, TR2.30
/TX2-: F45.2, J5.2, TR2.28
/TX2_F+: F73.2, J5.1
/TX3+: F47.1, F77.1, TR2.25
/TX3-: F47.2, J5.6, TR2.23
/TX3_F+: F77.2, J5.5
/TX4+: F1.1, F25.1, TR1.40
/TX4-: F1.2, J2.2, TR1.38
/TX4_F+: F25.2, J2.1
/TX5+: F3.1, F29.1, TR1.35
/TX5-: F3.2, J2.6, TR1.33
/TX5_F+: F29.2, J2.5
/TX6+: F5.1, F33.1, TR1.30
/TX6-: F5.2, J3.2, TR1.28
/TX6_F+: F33.2, J3.1
/TX7+: F7.1, F37.1, TR1.25
/TX7-: F7.2, J3.6, TR1.23
/TX7_F+: F37.2, J3.5
GND: C5.2, C6.2, C7.2, C8.2, C13.2, C14.2, C15.2, C16.2, J1.5, J1.6, J1.15, J1.16, J1.25, J1.26, J1.35, J1.36, U1.11, U2.11, U3.11, U4.11, U5.11, U6.11, U7.11, U8.11
unnamed: C1.1, TR1.1
unnamed: C2.1, TR1.6
unnamed: C3.1, TR1.11
unnamed: C4.1, TR1.16
unnamed: C5.1, TR1.4
unnamed: C6.1, TR1.9
unnamed: C7.1, TR1.14
unnamed: C8.1, TR1.19
unnamed: C9.1, TR2.1
unnamed: C10.1, TR2.6
unnamed: C11.1, TR2.11
unnamed: C12.1, TR2.16
unnamed: C13.1, TR2.4
unnamed: C14.1, TR2.9
unnamed: C15.1, TR2.14
unnamed: C16.1, TR2.19

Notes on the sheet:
Transformer requirements: Receive: 1:1 pri:sec turns ratio ("1:1CT") Center tap on secondary, connected to 100nF to GND Transmit: 1:2 pri:sec turns ratio ("1:2"), to step up voltage across secondary 680nF DC blocking on primary side TIP signal
ADIT600 transmits on pair 4-5.
TIP: Positive RING: Negative

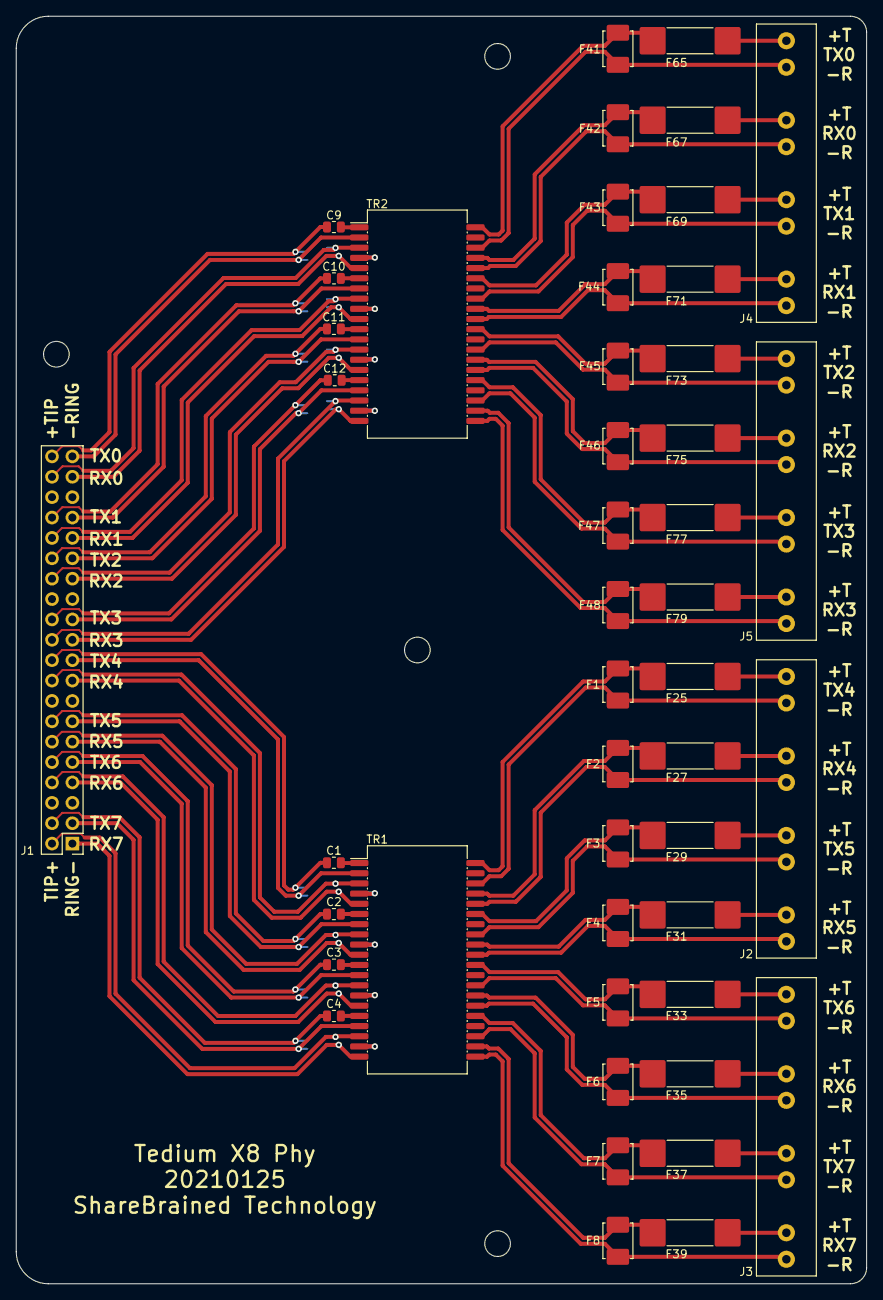
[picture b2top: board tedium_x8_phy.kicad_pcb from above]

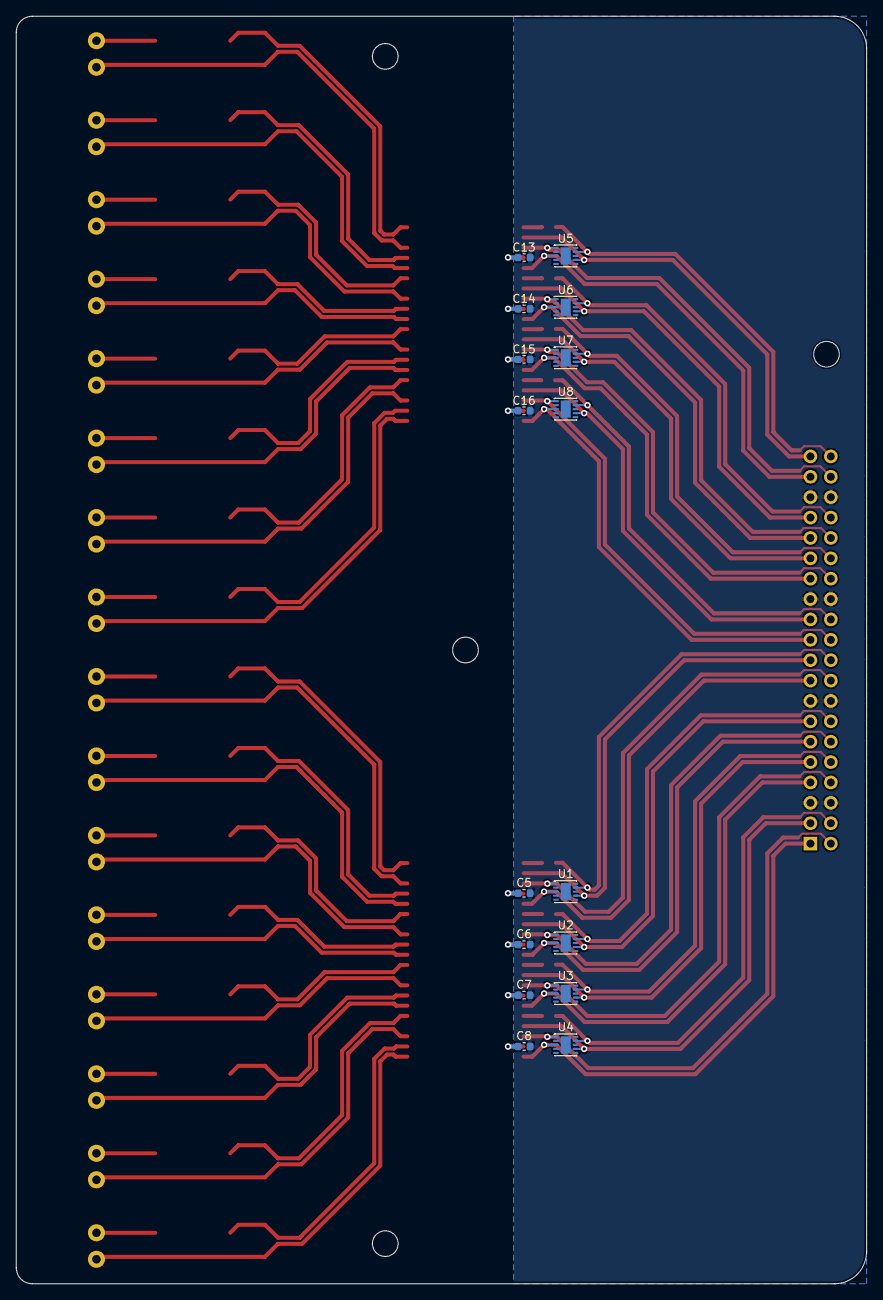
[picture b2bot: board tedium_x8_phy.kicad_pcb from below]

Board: 2 copper layers, 106.0 x 158.0 mm, 67 parts (16 on the bottom side), 97 nets.

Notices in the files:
breakout_xrt83l30/hw/breakout_xrt83l30.sch:
Copyright (C) 2019
hardware/breakout_xrt83l30/breakout_xrt83l30.kicad_pcb:
Copyright (C) 2019 Jared Boone
Licensed under CERN-OHL-P v2
hardware/tedium_x8/tedium_x8.kicad_pcb:
Copyright (C) 2020 Jared Boone
hardware/tedium_x8_phy/tedium_x8_phy.kicad_sch:
Copyright (C) 2021 Jared Boone
